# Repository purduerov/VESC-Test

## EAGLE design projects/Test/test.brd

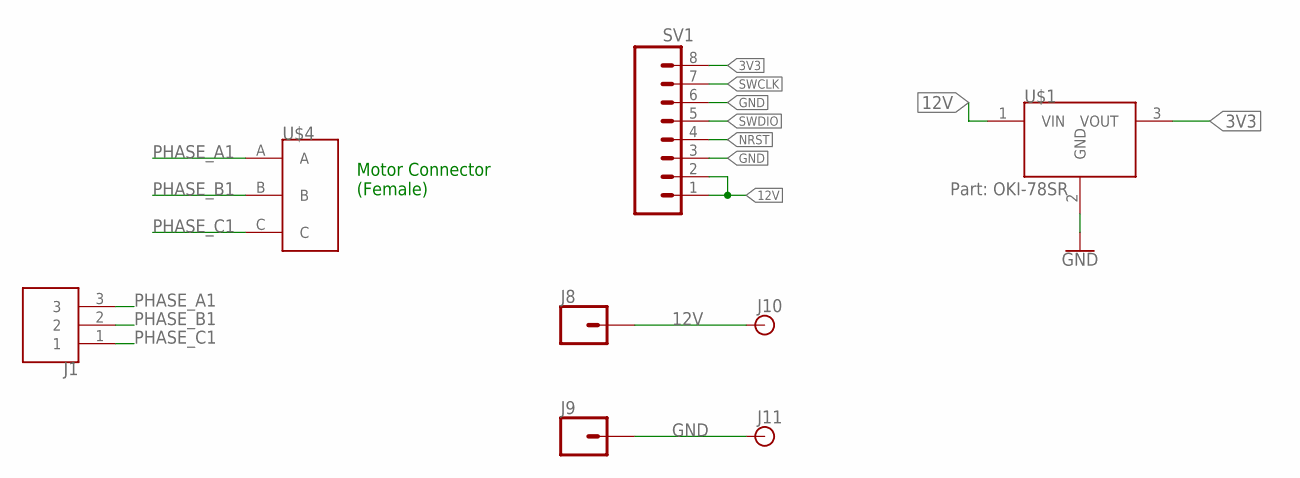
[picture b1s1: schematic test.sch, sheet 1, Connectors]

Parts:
J1: 284512-3
J8, J9: CONN_01; 1X01
J10, J11: BANANA_PTH; BANANA_CONN_NO_THERM
SV1: CONN_08"; 1X08
U$1: MURATA-DC-DC
U$4: 3PINCONNECTOR

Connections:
3V3: SV1.8, U$1.3 (VOUT)
12V: J8.1, J10.1, SV1.1, SV1.2, U$1.1 (VIN); also elsewhere on the board
GND: J9.1, J11.1, SV1.3, SV1.6, U$1.2 (GND); also elsewhere on the board
NRST: SV1.4; also elsewhere on the board
PHASE_A1: J1.3, U$4.A; also elsewhere on the board
PHASE_B1: J1.2, U$4.B; also elsewhere on the board
PHASE_C1: J1.1, U$4.C; also elsewhere on the board
SWCLK: SV1.7; also elsewhere on the board
SWDIO: SV1.5; also elsewhere on the board

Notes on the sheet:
Motor Connector (Female)

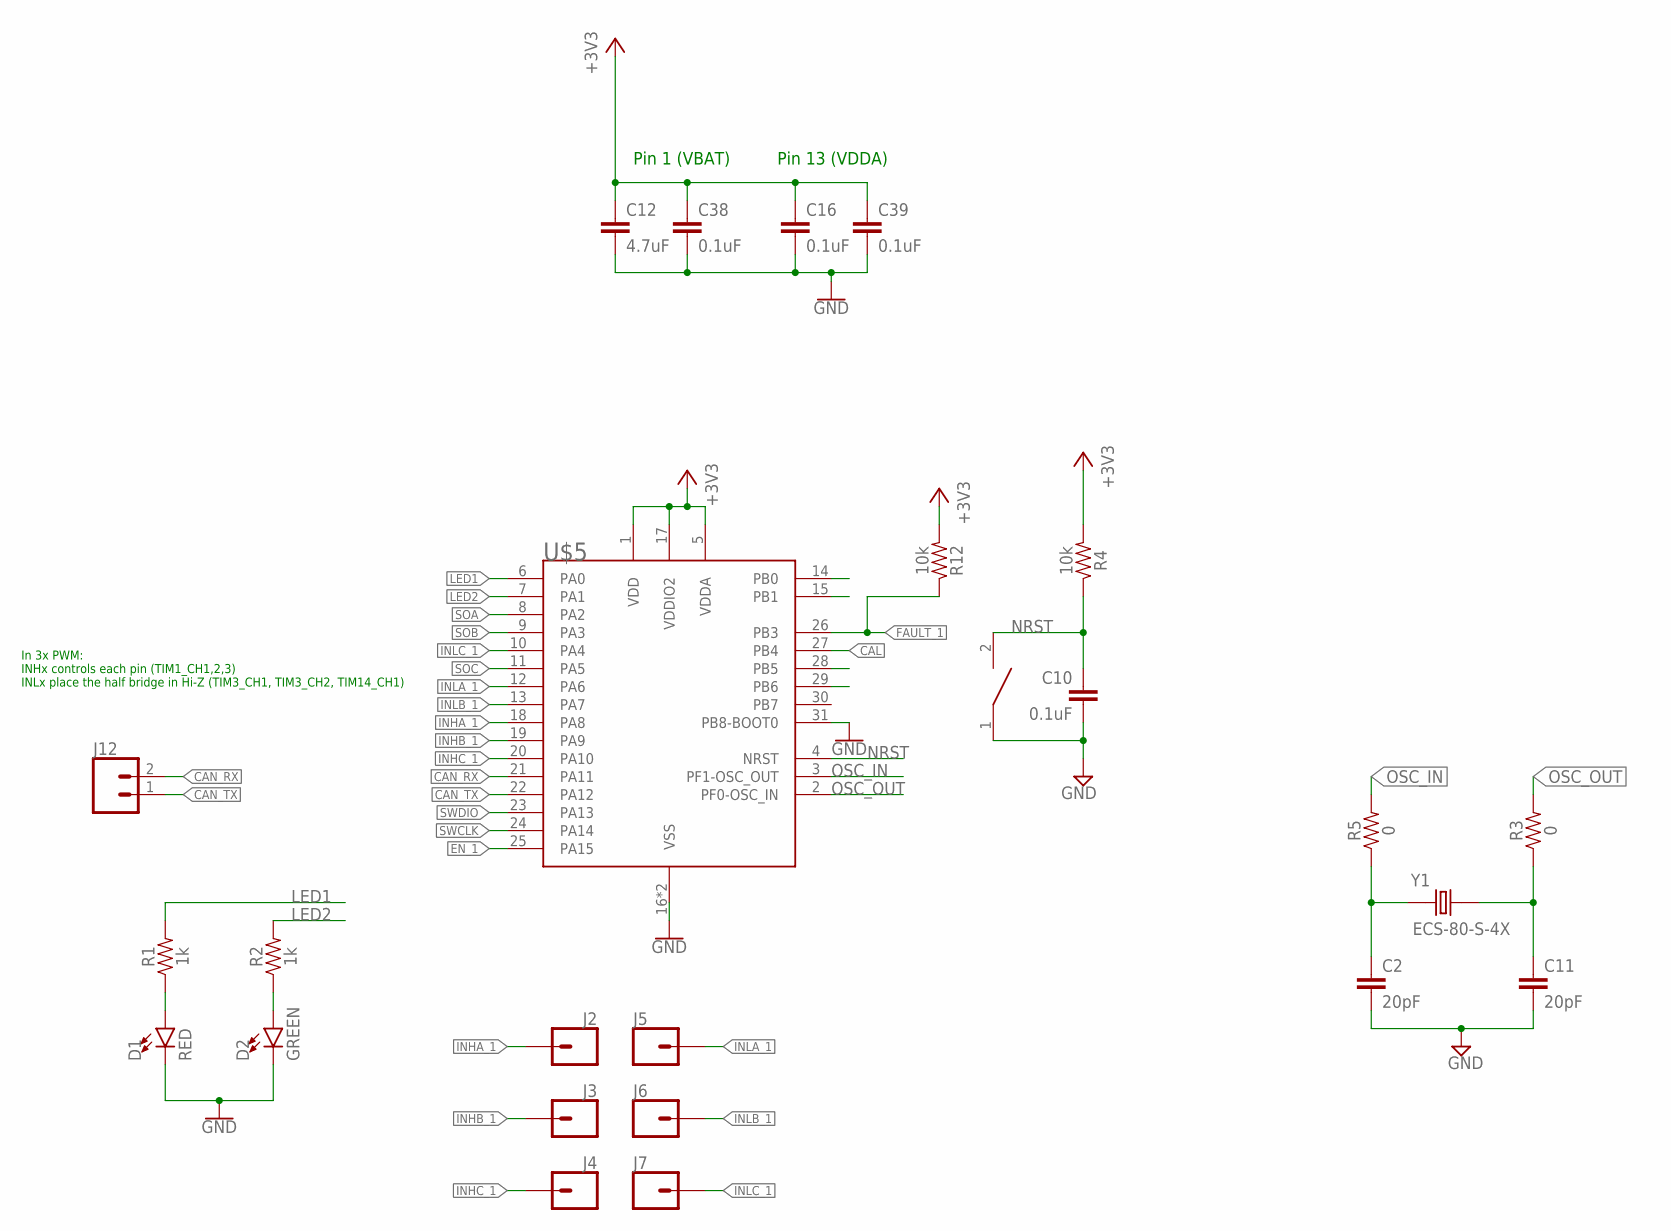
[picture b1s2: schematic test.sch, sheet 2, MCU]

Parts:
C2, C11: 20pF; 0603
C10, C16, C38, C39: 0.1uF; 0603
C12: 4.7uF; 0603
D1: RED; 0805
D2: GREEN; 0805
J2, J3, J4, J5, J6, J7: CONN_01; 1X01
J12: CONN_02; 1X02
R1, R2: 1k; 0603
R3, R5: 0; 0603
R4, R12: 10k; 0603
RESET1: DISCRETECOMPONENTS_SWITCH; DISCRETECOMPONENTS_SW_2512
U$5: STM32F042K6T6; LQFP32
Y1: ECS-80-S-4X; XTAL_ECS-80-S-4X

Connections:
+3V3: C12.1, C16.1, C38.1, C39.1, R4.2, R12.2, U$5.1 (VDD), U$5.5 (VDDA), U$5.17 (VDDIO2); also elsewhere on the board
CAL: U$5.27 (PB4); also elsewhere on the board
CAN_RX: J12.2, U$5.21 (PA11)
CAN_TX: J12.1, U$5.22 (PA12)
EN_1: U$5.25 (PA15); also elsewhere on the board
FAULT_1: R12.1, U$5.26 (PB3); also elsewhere on the board
GND: C2.2, C10.2, C11.2, C12.2, C16.2, C38.2, C39.2, D1.C, D2.C, RESET1.1, U$5.16 (VSS), U$5.31 (PB8-BOOT0), U$5.32 (VSS); also elsewhere on the board
INHA_1: J2.1, U$5.18 (PA8); also elsewhere on the board
INHB_1: J3.1, U$5.19 (PA9); also elsewhere on the board
INHC_1: J4.1, U$5.20 (PA10); also elsewhere on the board
INLA_1: J5.1, U$5.12 (PA6); also elsewhere on the board
INLB_1: J6.1, U$5.13 (PA7); also elsewhere on the board
INLC_1: J7.1, U$5.10 (PA4); also elsewhere on the board
LED1: R1.2, U$5.6 (PA0)
LED1_MID: D1.A, R1.1
LED2: R2.2, U$5.7 (PA1)
LED2_MID: D2.A, R2.1
NRST: C10.1, R4.1, RESET1.2, U$5.4 (NRST); also elsewhere on the board
OSC_IN: R5.2, U$5.3 (PF1-OSC_OUT)
OSC_OUT: R3.2, U$5.2 (PF0-OSC_IN)
OSC_XTAL_1: C2.1, R5.1, Y1.1
OSC_XTAL_2: C11.1, R3.1, Y1.2
SOA: U$5.8 (PA2); also elsewhere on the board
SOB: U$5.9 (PA3); also elsewhere on the board
SOC: U$5.11 (PA5); also elsewhere on the board
SWCLK: U$5.24 (PA14); also elsewhere on the board
SWDIO: U$5.23 (PA13); also elsewhere on the board

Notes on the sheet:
Pin 1 (VBAT)
Pin 13 (VDDA)
In 3x PWM: INHx controls each pin (TIM1_CH1,2,3) INLx place the half bridge in Hi-Z (TIM3_CH1, TIM3_CH2, TIM14_CH1)

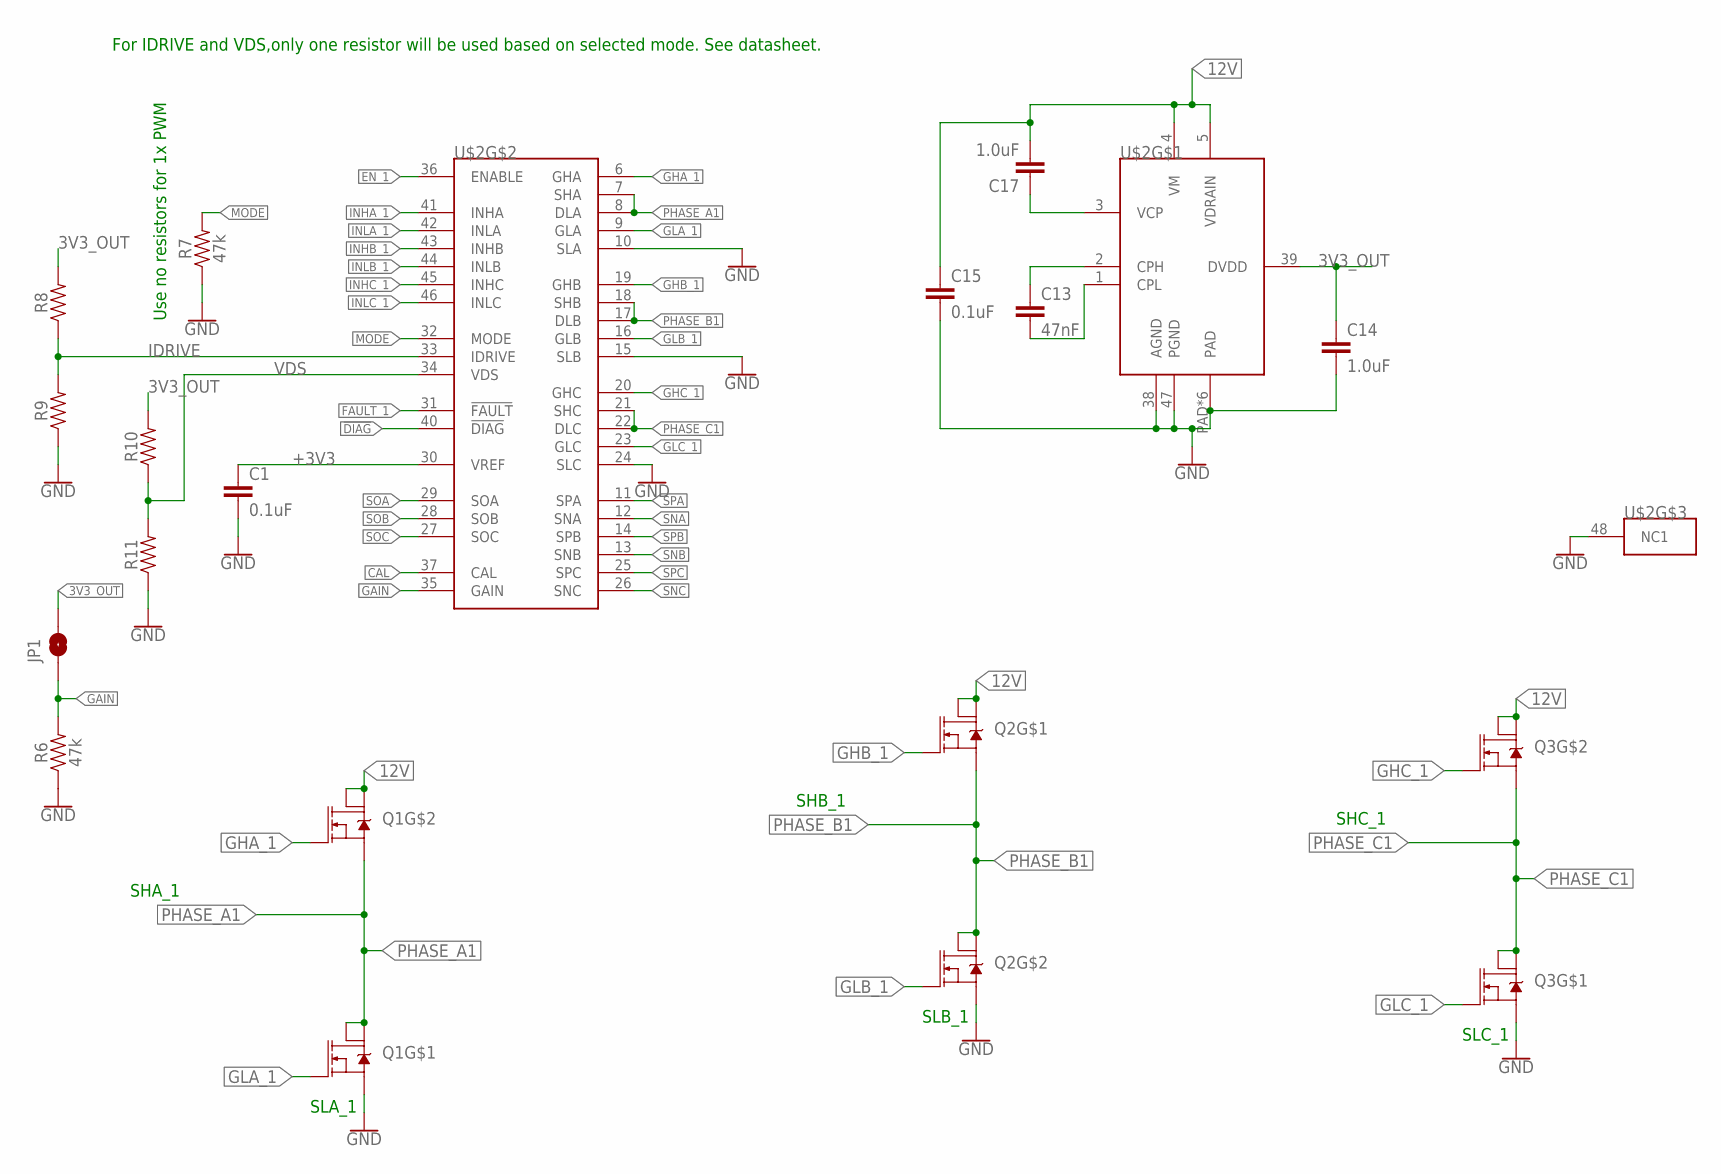
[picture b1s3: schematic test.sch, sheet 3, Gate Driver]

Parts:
C1, C15: 0.1uF; 0603
C13: 47nF; 0603
C14, C17: 1.0uF; 0603
JP1: JUMPER-SMT_2_NO_NO-SILK; SMT-JUMPER_2_NO_NO-SILK
Q1, Q2, Q3: DUAL-NMOS; SO08
R6, R7: 47k; 0603
R8, R9, R10, R11: 0603
U$2: DRV8343H; 48-TQFP-BOTTOM

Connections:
3V3_OUT: C14.1, JP1.2, R8.2, R10.2, U$2.39 (DVDD)
12V: C15.1, C17.2, Q1.5 (D1), Q1.6 (D2), Q2.7 (D1), Q2.8 (D2), Q3.5 (D1), Q3.6 (D2), U$2.4 (VM), U$2.5 (VDRAIN); also elsewhere on the board
!DIAG: U$2.40 (!DIAG)
+3V3: C1.1, U$2.30 (VREF); also elsewhere on the board
CAL: U$2.37 (CAL); also elsewhere on the board
CPH: C13.1, U$2.2 (CPH)
CPL: C13.2, U$2.1 (CPL)
EN_1: U$2.36 (ENABLE); also elsewhere on the board
FAULT_1: U$2.31 (!FAULT); also elsewhere on the board
GAIN: JP1.1, R6.2, U$2.35 (GAIN)
GHA_1: Q1.4 (G), U$2.6 (GHA)
GHB_1: Q2.2 (G), U$2.19 (GHB)
GHC_1: Q3.4 (G), U$2.20 (GHC)
GLA_1: Q1.2 (G), U$2.9 (GLA)
GLB_1: Q2.4 (G), U$2.16 (GLB)
GLC_1: Q3.2 (G), U$2.23 (GLC)
GND: C1.2, C14.2, C15.2, Q1.1 (S), Q2.3 (S), Q3.1 (S), R6.1, R7.1, R9.1, R11.1, U$2.10 (SLA), U$2.15 (SLB), U$2.24 (SLC), U$2.38 (AGND), U$2.47 (PGND), U$2.48 (NC1), U$2.PAD, U$2.PAD_BOT (PAD), U$2.PAD_CON1 (PAD), U$2.PAD_CON2 (PAD), U$2.PAD_CON3 (PAD), U$2.PAD_CON4 (PAD); also elsewhere on the board
IDRIVE: R8.1, R9.2, U$2.33 (IDRIVE)
INHA_1: U$2.41 (INHA); also elsewhere on the board
INHB_1: U$2.43 (INHB); also elsewhere on the board
INHC_1: U$2.45 (INHC); also elsewhere on the board
INLA_1: U$2.42 (INLA); also elsewhere on the board
INLB_1: U$2.44 (INLB); also elsewhere on the board
INLC_1: U$2.46 (INLC); also elsewhere on the board
MODE: R7.2, U$2.32 (MODE)
PHASE_A1: Q1.3 (S), Q1.7 (D1), Q1.8 (D2), U$2.7 (SHA), U$2.8 (DLA); also elsewhere on the board
PHASE_B1: Q2.1 (S), Q2.5 (D1), Q2.6 (D2), U$2.17 (DLB), U$2.18 (SHB); also elsewhere on the board
PHASE_C1: Q3.3 (S), Q3.7 (D1), Q3.8 (D2), U$2.21 (SHC), U$2.22 (DLC); also elsewhere on the board
SNA: U$2.12 (SNA)
SNB: U$2.13 (SNB)
SNC: U$2.26 (SNC)
SOA: U$2.29 (SOA); also elsewhere on the board
SOB: U$2.28 (SOB); also elsewhere on the board
SOC: U$2.27 (SOC); also elsewhere on the board
SPA: U$2.11 (SPA)
SPB: U$2.14 (SPB)
SPC: U$2.25 (SPC)
VDS: R10.1, R11.2, U$2.34 (VDS)
V_CAP_L: C17.1, U$2.3 (VCP)

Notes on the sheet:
For IDRIVE and VDS,only one resistor will be used based on selected mode. See datasheet.
SLA_1
SLB_1
SLC_1
SHA_1
SHB_1
SHC_1
Use no resistors for 1x PWM

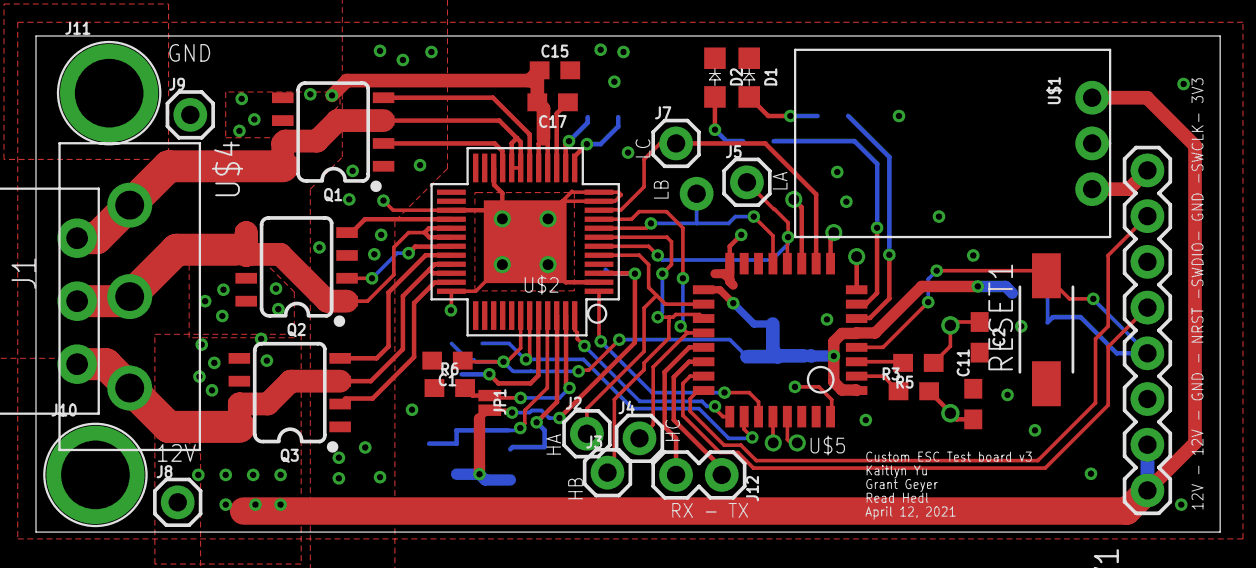
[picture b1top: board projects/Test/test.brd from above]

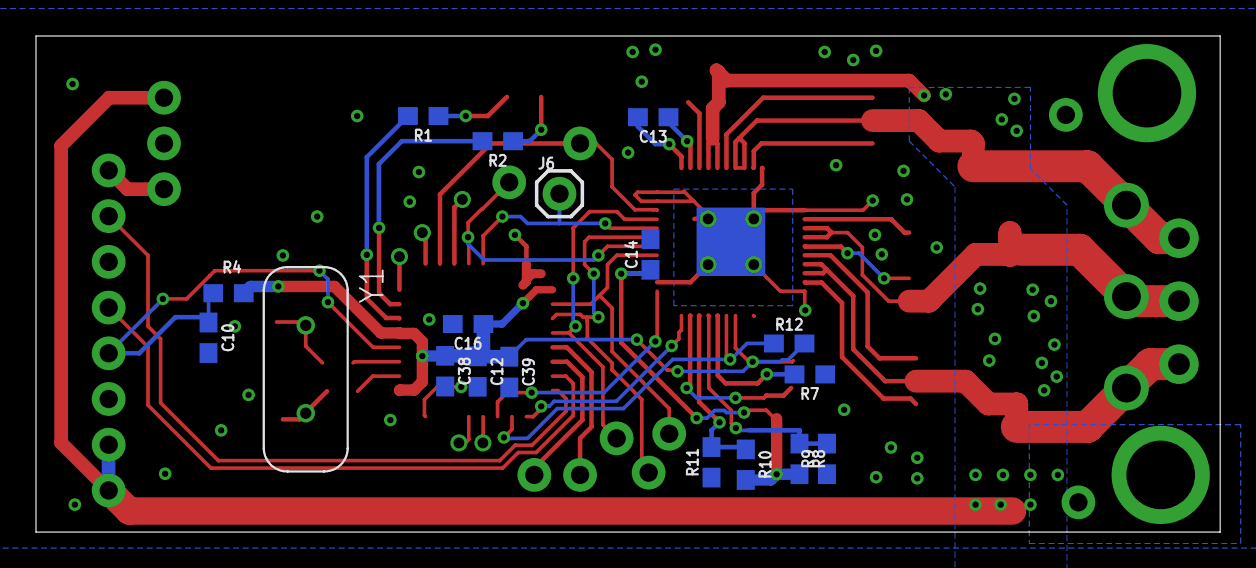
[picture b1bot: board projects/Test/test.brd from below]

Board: 2 copper layers, 65.8 x 27.6 mm, 49 parts (18 on the bottom side), 46 nets.

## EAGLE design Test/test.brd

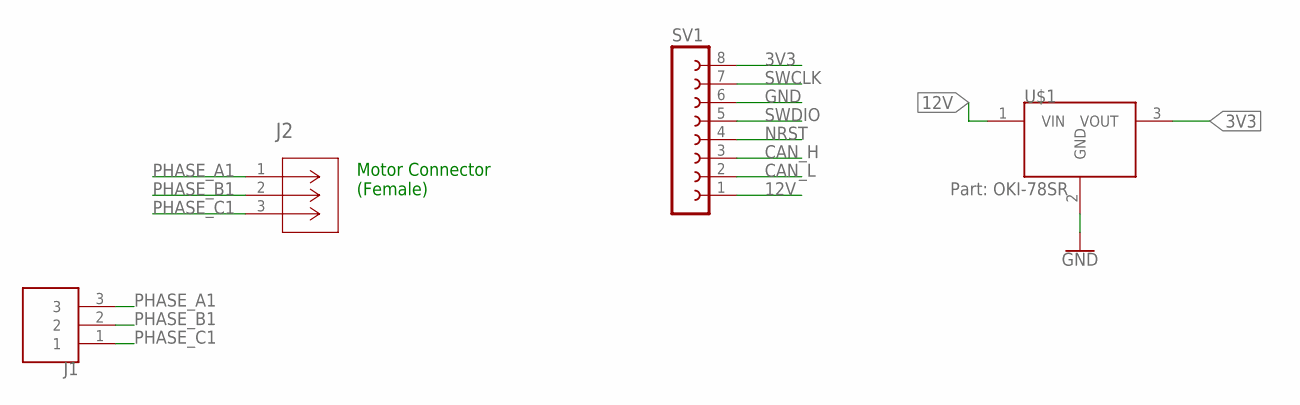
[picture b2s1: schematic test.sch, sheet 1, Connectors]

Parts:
J1: 284512-3
J2: 1755529; CONN_1755529
SV1: FE08-1; FE08
U$1: MURATA-DC-DC

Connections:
3V3: SV1.8, U$1.3 (VOUT); also elsewhere on the board
12V: SV1.1, U$1.1 (VIN); also elsewhere on the board
CAN_H: SV1.3; also elsewhere on the board
CAN_L: SV1.2; also elsewhere on the board
GND: SV1.6, U$1.2 (GND); also elsewhere on the board
NRST: SV1.4; also elsewhere on the board
PHASE_A1: J1.3, J2.1; also elsewhere on the board
PHASE_B1: J1.2, J2.2; also elsewhere on the board
PHASE_C1: J1.1, J2.3; also elsewhere on the board
SWCLK: SV1.7; also elsewhere on the board
SWDIO: SV1.5; also elsewhere on the board

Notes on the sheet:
Motor Connector (Female)

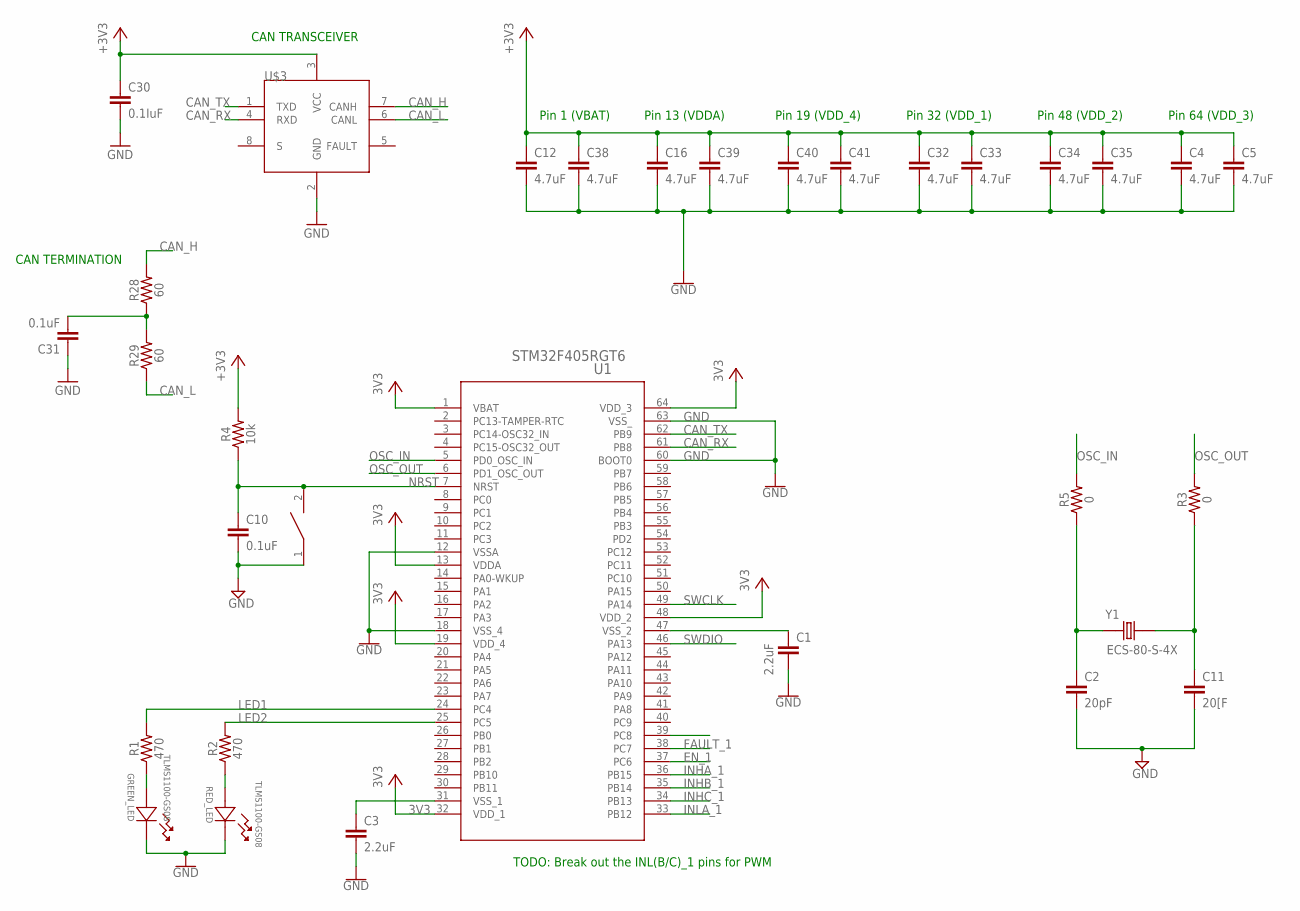
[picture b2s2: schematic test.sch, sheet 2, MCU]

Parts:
C1, C3: 2.2uF; 0603
C2: 20pF; 0603
C4, C5, C12, C16, C32, C33, C34, C35, C38, C39, C40, C41: 4.7uF; 0603
C10, C31: 0.1uF; 0603
C11: 20[F; 0603
C30: 0.1IuF; 0603
GREEN_LED: TLMS1100-GS08; LED_VISHAY_TLMX1100
R1, R2: 470; 0603
R3, R5: 0; 0603
R4: 10k; 0603
R28, R29: 60; 0603
RED_LED: TLMS1100-GS08; LED_VISHAY_TLMX1100
RESET1: DISCRETECOMPONENTS_SWITCH; DISCRETECOMPONENTS_SW_2512
U1: STM32F405RGT6; LQFP-64
U$3: TCAN337D; SOIC-8
Y1: ECS-80-S-4X; XTAL_ECS-80-S-4X

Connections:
3V3: C4.1, C5.1, C12.1, C16.1, C30.1, C32.1, C33.1, C34.1, C35.1, C38.1, C39.1, C40.1, C41.1, R4.2, U1.1 (VBAT), U1.13 (VDDA), U1.19 (VDD_4), U1.32 (VDD_1), U1.48 (VDD_2), U1.64 (VDD_3), U$3.3 (VCC); also elsewhere on the board
CAN_H: R28.2, U$3.7 (CANH); also elsewhere on the board
CAN_L: R29.1, U$3.6 (CANL); also elsewhere on the board
CAN_RX: U1.61 (PB8), U$3.4 (RXD)
CAN_TX: U1.62 (PB9), U$3.1 (TXD)
EN_1: U1.37 (PC6); also elsewhere on the board
FAULT_1: U1.38 (PC7); also elsewhere on the board
GND: C1.2, C2.2, C3.2, C4.2, C5.2, C10.2, C11.2, C12.2, C16.2, C30.2, C31.1, C32.2, C33.2, C34.2, C35.2, C38.2, C39.2, C40.2, C41.2, GREEN_LED.1, RED_LED.1, RESET1.1, U1.12 (VSSA), U1.18 (VSS_4), U1.60 (BOOT0), U1.63 (VSS_), U$3.2 (GND); also elsewhere on the board
INHA_1: U1.36 (PB15); also elsewhere on the board
INHB_1: U1.35 (PB14); also elsewhere on the board
INHC_1: U1.34 (PB13); also elsewhere on the board
INLA_1: U1.33 (PB12); also elsewhere on the board
INL_2: U1.39 (PC8)
LED1: R1.2, U1.24 (PC4)
LED1_MID: GREEN_LED.2, R1.1
LED2: R2.2, U1.25 (PC5)
LED2_MID: R2.1, RED_LED.2
unnamed: C1.1, U1.47 (VSS_2)
unnamed: C3.1, U1.31 (VSS_1)
unnamed: C11.1, R3.1, Y1.2
unnamed: C2.1, R5.1, Y1.1
unnamed: C31.2, R28.1, R29.2
NRST: C10.1, R4.1, RESET1.2, U1.7 (NRST); also elsewhere on the board
OSC_IN: R5.2, U1.5 (PD0_OSC_IN)
OSC_OUT: R3.2, U1.6 (PD1_OSC_OUT)
SWCLK: U1.49 (PA14); also elsewhere on the board
SWDIO: U1.46 (PA13); also elsewhere on the board

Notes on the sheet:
Pin 1 (VBAT)
Pin 13 (VDDA)
Pin 19 (VDD_4)
Pin 32 (VDD_1)
Pin 48 (VDD_2)
Pin 64 (VDD_3)
CAN TRANSCEIVER
CAN TERMINATION
TODO: Break out the INL(B/C)_1 pins for PWM

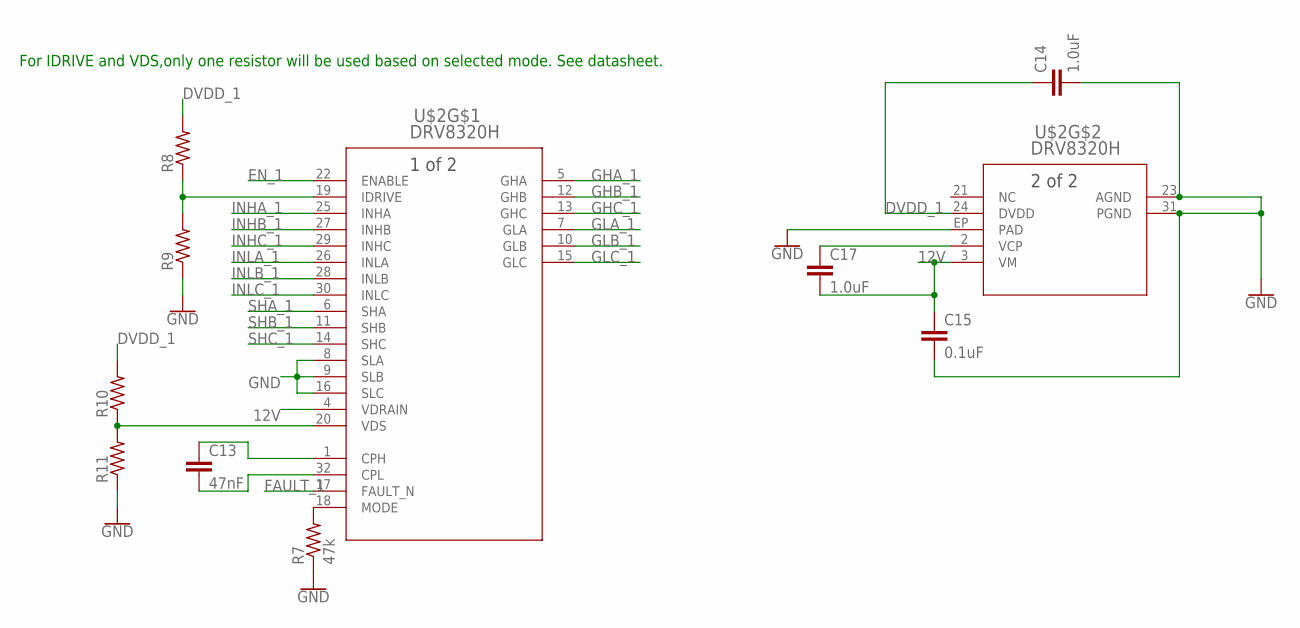
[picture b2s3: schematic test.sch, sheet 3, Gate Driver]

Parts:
C13: 47nF; 0603
C14, C17: 1.0uF; 0603
C15: 0.1uF; 0603
R7: 47k; R0603
R8, R9, R10, R11: R-US_R0603; R0603
U$2: DRV8320H; QFN-32-5X5MM

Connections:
12V: C15.1, C17.2, U$2.3 (VM), U$2.4 (VDRAIN); also elsewhere on the board
DVDD_1: C14.1, R8.2, R10.2, U$2.24 (DVDD)
EN_1: U$2.22 (ENABLE); also elsewhere on the board
FAULT_1: U$2.17 (FAULT_N); also elsewhere on the board
GHA_1: U$2.5 (GHA); also elsewhere on the board
GHB_1: U$2.12 (GHB); also elsewhere on the board
GHC_1: U$2.13 (GHC); also elsewhere on the board
GLA_1: U$2.7 (GLA); also elsewhere on the board
GLB_1: U$2.10 (GLB); also elsewhere on the board
GLC_1: U$2.15 (GLC); also elsewhere on the board
GND: C14.2, C15.2, R7.1, R9.1, R11.1, U$2.8 (SLA), U$2.9 (SLB), U$2.16 (SLC), U$2.23 (AGND), U$2.31 (PGND), U$2.EP (PAD); also elsewhere on the board
INHA_1: U$2.25 (INHA); also elsewhere on the board
INHB_1: U$2.27 (INHB); also elsewhere on the board
INHC_1: U$2.29 (INHC); also elsewhere on the board
INLA_1: U$2.26 (INLA); also elsewhere on the board
INLB_1: U$2.28 (INLB)
INLC_1: U$2.30 (INLC)
unnamed: C13.1, U$2.1 (CPH)
unnamed: C13.2, U$2.32 (CPL)
unnamed: R8.1, R9.2, U$2.19 (IDRIVE)
unnamed: R7.2, U$2.18 (MODE)
unnamed: R10.1, R11.2, U$2.20 (VDS)
unnamed: C17.1, U$2.2 (VCP)
SHA_1: U$2.6 (SHA); also elsewhere on the board
SHB_1: U$2.11 (SHB); also elsewhere on the board
SHC_1: U$2.14 (SHC); also elsewhere on the board

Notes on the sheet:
For IDRIVE and VDS,only one resistor will be used based on selected mode. See datasheet.

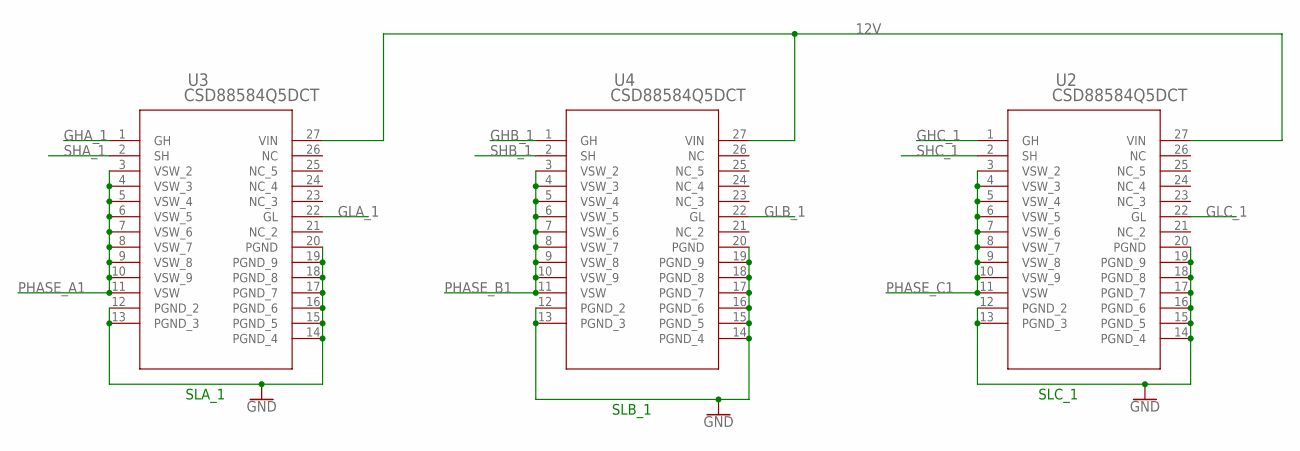
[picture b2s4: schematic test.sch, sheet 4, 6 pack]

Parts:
U2, U3, U4: CSD88584Q5DCT; DMM0022A

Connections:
12V: U2.27 (VIN), U3.27 (VIN), U4.27 (VIN); also elsewhere on the board
GHA_1: U3.1 (GH); also elsewhere on the board
GHB_1: U4.1 (GH); also elsewhere on the board
GHC_1: U2.1 (GH); also elsewhere on the board
GLA_1: U3.22 (GL); also elsewhere on the board
GLB_1: U4.22 (GL); also elsewhere on the board
GLC_1: U2.22 (GL); also elsewhere on the board
GND: U2.12 (PGND_2), U2.13 (PGND_3), U2.14 (PGND_4), U2.15 (PGND_5), U2.16 (PGND_6), U2.17 (PGND_7), U2.18 (PGND_8), U2.19 (PGND_9), U2.20 (PGND), U3.12 (PGND_2), U3.13 (PGND_3), U3.14 (PGND_4), U3.15 (PGND_5), U3.16 (PGND_6), U3.17 (PGND_7), U3.18 (PGND_8), U3.19 (PGND_9), U3.20 (PGND), U4.12 (PGND_2), U4.13 (PGND_3), U4.14 (PGND_4), U4.15 (PGND_5), U4.16 (PGND_6), U4.17 (PGND_7), U4.18 (PGND_8), U4.19 (PGND_9), U4.20 (PGND); also elsewhere on the board
PHASE_A1: U3.3 (VSW_2), U3.4 (VSW_3), U3.5 (VSW_4), U3.6 (VSW_5), U3.7 (VSW_6), U3.8 (VSW_7), U3.9 (VSW_8), U3.10 (VSW_9), U3.11 (VSW); also elsewhere on the board
PHASE_B1: U4.3 (VSW_2), U4.4 (VSW_3), U4.5 (VSW_4), U4.6 (VSW_5), U4.7 (VSW_6), U4.8 (VSW_7), U4.9 (VSW_8), U4.10 (VSW_9), U4.11 (VSW); also elsewhere on the board
PHASE_C1: U2.3 (VSW_2), U2.4 (VSW_3), U2.5 (VSW_4), U2.6 (VSW_5), U2.7 (VSW_6), U2.8 (VSW_7), U2.9 (VSW_8), U2.10 (VSW_9), U2.11 (VSW); also elsewhere on the board
SHA_1: U3.2 (SH); also elsewhere on the board
SHB_1: U4.2 (SH); also elsewhere on the board
SHC_1: U2.2 (SH); also elsewhere on the board

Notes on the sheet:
SLA_1
SLB_1
SLC_1

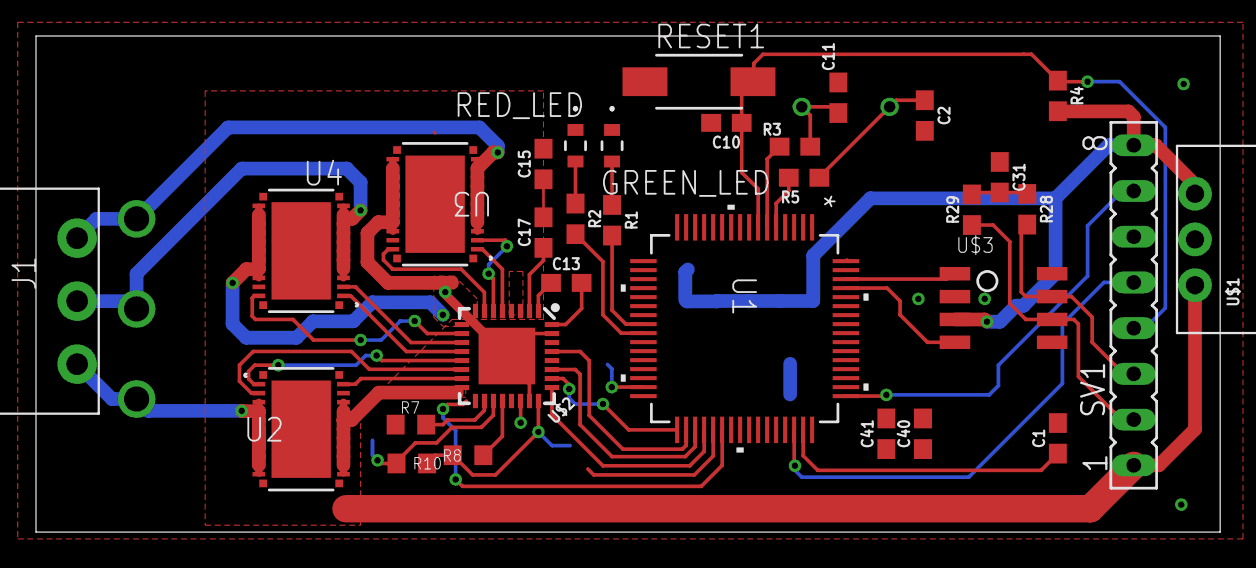
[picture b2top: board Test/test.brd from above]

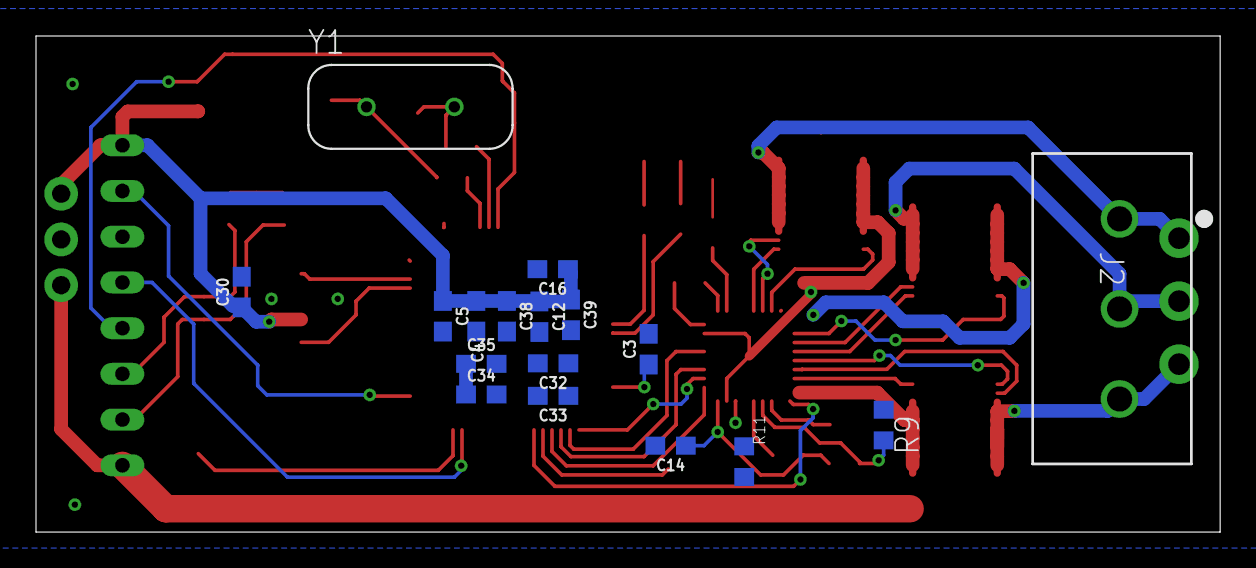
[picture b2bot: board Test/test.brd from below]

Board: 2 copper layers, 65.8 x 27.6 mm, 49 parts (17 on the bottom side), 46 nets.

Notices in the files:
parts and their libraries:
SparkFun-Capacitors: Licensing: Creative Commons ShareAlike 4.0 International - https://creativecommons.org/licenses/by-sa/4.0
